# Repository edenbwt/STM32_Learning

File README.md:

# KiCad & STM32 Projects

This repository is a collection of my personal projects for learning microelectronics and hardware coding, using KiCad for PCB design and STM32 for embedded systems programming.

## Project Overview

Each project folder contains:
- **KiCad files**: Schematics and PCB layouts.
- **STM32 Code**: Firmware for STM32 microcontrollers.

## Tools Used
- **KiCad**: PCB design tool.
- **STM32CubeIDE**: For developing and programming STM32 microcontrollers.

## Projects

| Project | Description |
| ------- | ----------- |
| Project 1 | My first project using KiCad and STM32, the base is a STM32F405RGT6 powerded by a usb type-c cable |

This repository is for personal use, documenting my progress in learning.

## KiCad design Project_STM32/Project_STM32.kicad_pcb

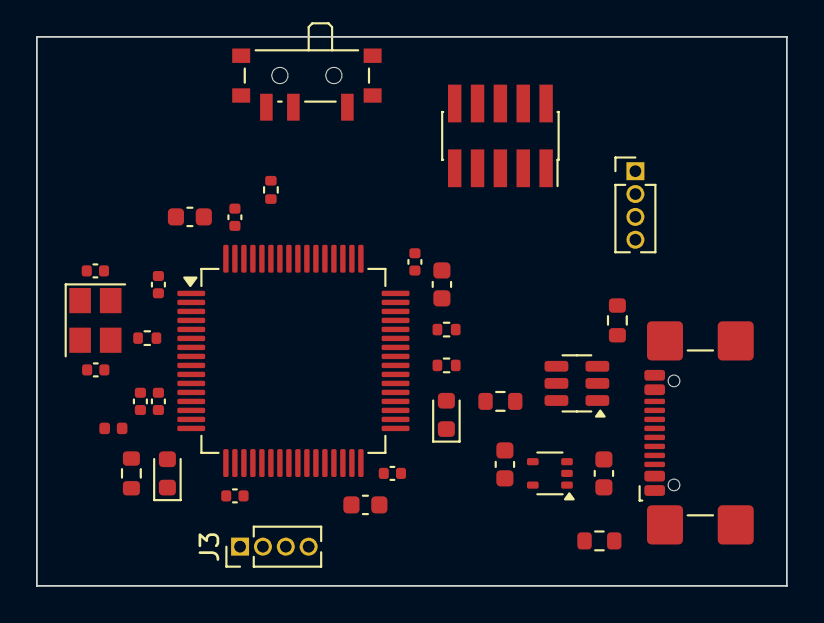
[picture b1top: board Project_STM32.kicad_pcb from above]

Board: 4 copper layers, 41.7 x 30.5 mm, 34 parts (0 on the bottom side), 28 nets, no tracks yet.

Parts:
C1, C2: 2u2; C_0603_1608Metric
C3, C12, C13: 4u7; C_0603_1608Metric
C4, C5, C6, C7, C14: 100n; C_0402_1005Metric
C8: 1u; C_0402_1005Metric
C9: 10n; C_0402_1005Metric
C10, C11: 12p; C_0402_1005Metric
D1: LED_green; LED_0603_1608Metric
D2: LED_Bleu_Power; LED_0603_1608Metric
J1: Serial_Debug_Conn; PinSocket_2x05_P1.27mm_Vertical_SMD
J2, J3: Conn_01x04_Pin; PinHeader_1x04_P1.27mm_Vertical
J4: USB_C_Receptacle_USB2.0_16P; USB_C_Receptacle_GCT_USB4110
L2: L_Small; L_0402_1005Metric
R1: 10k; R_0402_1005Metric
R2: 47; R_0402_1005Metric
R3, R4: 1k5; R_0603_1608Metric
R9, R10: 2k2; R_0402_1005Metric
R12, R13: 5k1; R_0603_1608Metric
SW1: SW_SPDT; SW_SPDT_PCM12
U1: STM32F405RGT6; LQFP-64_10x10mm_P0.5mm
U2: MIC5366-3.3YC5; SOT-353_SC-70-5
U3: USBLC6-2SC6; SOT-23-6
Y1: 16MH; Crystal_SMD_3225-4Pin_3.2x2.5mm

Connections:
+3.3V: C3.1, C4.1, C5.1, C6.1, C7.1, C13.1, C14.1, J1.1, J2.4, J3.4, L2.1, R4.1, R9.1, R10.1, SW1.1 (A), U1.1 (VBAT), U1.19 (VDD), U1.32 (VDD), U1.48 (VDD), U1.64 (VDD), U2.5 (VOUT)
+3.3VA: C8.1, C9.1, L2.2, U1.13 (VDDA)
+5V: C12.1, J4.A4 (VBUS), J4.A9 (VBUS), J4.B4 (VBUS), J4.B9 (VBUS), U2.1 (VIN), U2.3 (EN), U3.5 (VBUS)
BOOTO: R1.2, U1.60 (BOOT0)
GND: C1.2, C2.2, C3.2, C4.2, C5.2, C6.2, C7.2, C8.2, C9.2, C10.2, C11.2, C12.2, C13.2, C14.2, D2.1 (K), J1.3, J1.5, J1.9, J2.1, J3.1, J4.A1 (GND), J4.A12 (GND), J4.B1 (GND), J4.B12 (GND), J4.S1 (SHIELD), R3.2, R12.2, R13.2, SW1.3 (C), U1.12 (VSSA), U1.18 (VSS), U1.63 (VSS), U2.2 (GND), U3.2 (GND), Y1.2, Y1.4
HSE_IN: C11.1, U1.5 (PH0), Y1.1
HSE_OUT: R2.1, U1.6 (PH1)
I2C_SCL: J2.3, R9.2, U1.41 (PA8)
I2C_SDA: J2.2, R10.2, U1.42 (PA9)
NSRT: J1.10, U1.7 (NRST)
unnamed: C10.1, R2.2, Y1.3
unnamed: D1.1 (K), R3.1
unnamed: D2.2 (A), R4.2
unnamed: J4.A6 (D+), J4.B6 (D+), U3.3 (I/O2)
unnamed: J4.A7 (D-), J4.B7 (D-), U3.1 (I/O1)
unnamed: R1.1, SW1.2 (B)
unnamed: C2.1, U1.31 (VCAP_1)
unnamed: C1.1, U1.47 (VCAP_2)
STATUS_LED: D1.2 (A), U1.16 (PA2)
SWCLOCK: J1.4, U1.49 (PA14)
SWDI: J1.2, U1.46 (PA13)
SWO: J1.6, U1.55 (PB3)
UART_RX: J3.3, U1.30 (PB11)
UART_TX: J3.2, U1.29 (PB10)
USB_D+: U1.45 (PA12), U3.4 (I/O2)
USB_D-: U1.44 (PA11), U3.6 (I/O1)
cc1: J4.A5 (CC1), R12.1
cc2: J4.B5 (CC2), R13.1

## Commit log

2024-09-08 added basic stm32 powerd by a usb typr c connector
2024-09-08 added the .net file for the compnent size
2024-09-08 general shape of the board done, fix small issues
